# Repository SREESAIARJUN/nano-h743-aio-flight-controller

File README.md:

# STM32H743 Nano Flight Controller + 4-in-1 ESC AIO

**Autonomous Engineering Release - Cycle 31**  
*Dense 36 × 36 mm AIO (30.5 × 30.5 mm M3 mount) for ArduPilot & PX4 with Integrated 4x 20A/35A ESC. Rev 8.0 moved off the 25.5 mm outline because 24 SOP-Advance MOSFETs cannot fit on it; see the Rev 8.0 changelog.*

---

## 1. System Overview
- **MCU**: STM32H743VIT6 (480 MHz ARM Cortex-M7, 2MB Flash, 1MB RAM, Double-Precision FPU), clocked from a 24 MHz HSE crystal. 480 MHz requires revision V silicon.
- **PCB Stackup**: 6 layers, JLCPCB JLC061612-1080, 1.614 mm, ENIG. 1 oz outer for signals and fine pitch, 2 oz inner planes (In1 GND / In2 VBAT / In3 VBAT / In4 GND), filled-and-capped via-in-pad (POFV, IPC-4761 Type VII). Through vias only, no HDI microvias.
- **Dual IMUs**:
  - Primary: ICM-42688-P on high-speed SPI1 with isolated ground plane and silicon damping pads.
  - Secondary: ICM-42688-P on SPI4 for redundancy and sensor voting.
- **Barometer**: Bosch / Infineon DPS310 high-precision baro on I2C1 with acoustic dampening.
- **OSD**: AT7456E analog OSD on SPI2 + dedicated 6-pin SH1.0 connector for DJI O3 / Walksnail Avatar / HDZero digital VTX.
- **DroneCAN / UAVCAN**: On-board TCAN334 CAN FD transceiver on FDCAN1.
- **Blackbox**: MicroSD card slot with 4-bit high-speed SDIO (SDMMC1).
- **Integrated 4-in-1 ESC**:
  - 4x Brushless ESC channels, 2S–4S LiPo input. **Rev 9 thermal rating per motor, all four loaded, 24 kHz PWM:** 20 A continuous / 25 A for 10 s in typical prop wash; 16 A / 21 A in the pessimistic case. 35 A is held for only ~2.4 s, and only ~8 A is allowed on a static bench. These figures require 12 AWG battery and 20 AWG motor leads. Rev 9 lowered them from 20/28 and 17/22 A once the FD6288Q's built-in dead time was included in the loss model.
  - 24x Toshiba TPHR8504PL 40 V N-MOSFETs, SOP Advance. RDS(on) max 0.85 mΩ at VGS=10 V and 1.40 mΩ at 4.5 V, Rth(ch-c) 0.88 K/W. ESC1/2 sit on the top face and ESC3/4 on the bottom; each half-bridge site is shared by both faces, and every high-side pair has a 16-via POFV thermal array.
  - 4x AT32F421K8U7 ESC MCUs running AM32 (target `NANO_H743_AIO_F421`), each driving one FD6288Q 3-phase gate driver. The FD6288Q has no internal bootstrap diode, so each phase has an external low-leakage Schottky, 2.2 Ω and 2.2 µF. Each gate has a 0 Ω series footprint (kept so the slew rate can be re-tuned at bring-up) and a 2.2 nF C0G Cgs. AM32 `DEAD_TIME 43` (358 ns) adds to the driver's fixed 100–300 ns dead time. The FC battery failsafe `BATT_CRT_VOLT 6.4` protects the driver's UVLO (Rev 9).
  - 0.5 mΩ shunt resistor with INA226 / INA169 current monitor. **Rev 8 finding:** at 4 × 20 A, D=0.9 (72 A battery current) it dissipates 2.6 W, which is over the 2 W rating previously specified. It needs a ≥ 4 W part or 0.25 mΩ; this is an open item.
  - Support for BLHeli_32 / AM32 firmware, DShot300/600/1200, and bi-directional DShot RPM filtering.

---

## 2. Repository Contents
- `kicad/`: KiCad 8 project. The schematic covers the MCU core (Rev 7). The 6-layer PCB has the stackup, planes and the 24-MOSFET power stage (Rev 8); the other functions are not placed yet. Project footprint library `nano-h743-aio.pretty`, custom DRC rules `nano-h743-aio.kicad_dru`.
- `kicad/gerbers/`: Gerber X2 for 6 copper layers plus paste, mask, silk and edge, Excellon PTH/NPTH with drill maps, and a Gerber job file carrying the stackup. These are a power-stage fab preview, **not a releasable board yet** (see Rev 8.0 open items).
- `ardupilot/`: ArduPilot board definition `hwdef.dat`, bootloader `hwdef-bl.dat`, and board `defaults.parm`.
- `tools/validate_dma.py`: DMA-allocation validator that runs ArduPilot's own `chibios_hwdef.py` / `dma_resolver.py` and enforces the stream policy.
- `tools/gen_mcu_core_sch.py`: generates the MCU-core schematic, project symbol library and `sym-lib-table` from `ardupilot/hwdef.dat` (Rev 7).
- `tools/verify_mcu_core_sch.py`: schematic gate covering KiCad ERC, netlist topology of the HSE and VDDA circuits, and the hwdef ↔ schematic pin map (Rev 7).
- `analysis/hse_vdda_analysis.py`: design check for the 24 MHz crystal and the VDDA filter (clock tree, load capacitance, gm_crit, drive level, LC damping). Writes `analysis/hse_vdda_report.json`.
- `am32_esc/am32_target.h`: AM32 `Inc/targets.h` block for the AT32F421 + FD6288Q channel (Rev 9).
- `am32_esc/gate_drive_design.py`: FD6288Q/TPHR8504PL gate-drive design (gate-resistor sweep, dead-time derivation, DTG encoding, driver and bootstrap checks). It checks `am32_target.h` and `eeprom_settings.json` against the derived values and writes `gate_drive_report.json`, which the thermal model reads (Rev 9).
- `am32_esc/eeprom_settings.json`: the AM32 EEPROM fields the analysis depends on (PWM frequency, complementary PWM, minimum duty, brake dead-time override, cutoffs), with offsets (Rev 9).
- `tools/am32_build_target.sh`: splices the target into an AM32 checkout, builds it with AM32's pinned toolchain, checks the resolved macros and runs a SITL twin (Rev 9).
- `tools/gen_power_stage_pcb.py`: generates the footprint library, DRC rules, project rules and the 6-layer board (Rev 8).
- `tools/verify_power_stage_pcb.py`: PCB gate covering stackup, MOSFET population, thermal via geometry, through-hole net safety, topology, DRC with a rule-liveness check, regeneration, fab outputs and the thermal report (Rev 8).
- `analysis/thermal_power_analysis.py`: per-MOSFET loss model and a thermal network that reads its geometry back from the KiCad board. Writes `thermal_report.json` and `thermal_dissipation_curve.png` (rewritten in Rev 8).
- `firmware/bdshot_telem/`: bidirectional DShot telemetry reference in C++. It is bit-exact with ArduPilot's GCR/eRPM decode, and adds EDT decoding, round-robin health and plausibility tracking, and notch planning. `make test` runs 46 checks under ASan/UBSan (Rev 10).
- `tools/validate_bdshot.py`: bidir-DShot gate run against an ArduPilot tree. It covers the generated DMA/IC config, capture coverage, parameter validity, a bit-exact decoder cross-check, unit tests, analysis gates and the upstream patch (Rev 10).
- `analysis/bdshot_timing_analysis.py`: TIM1/DShot600/GCR timing, round-robin eRPM rates, notch-lag sweep over `SERVO_DSHOT_RATE`, quantisation and line electricals. Writes `bdshot_report.json` (Rev 10).
- `ardupilot/patches/`: upstream ArduPilot fix for bdshot `RECV_FAILED` error attribution (Rev 10).

---

## Revision 10.0 Engineering Changelog

**Scope:** Bidirectional DShot600 RPM filtering. Covers the ArduPilot TIM1 timer-channel and input-capture configuration, and processing of the ESC telemetry fed back from the motors. Every claim below was checked against ArduPilot 4.7.1 source (`AP_HAL_ChibiOS/RCOutput_bdshot.cpp`, `RCOutput.cpp`, `chibios_hwdef.py`, `dma_resolver.py`, `Filter/HarmonicNotchFilter.cpp`, `AP_ESC_Telem`, `AP_Vehicle`). An independent adversarial review then went over the claims, and its corrections are included.

### Changes implemented

**1. TIM1 timer-channel / input-capture configuration (`ardupilot/hwdef.dat`).** The pin assignment stays `PE9/PE11/PE13/PE14 = TIM1_CH1..CH4`, with `BIDIR` on CH1 and CH3. The block now records why that set is complete and how it actually works, and `tools/validate_bdshot.py` proves it against the generated `hwdef.h`:
- **Capture pairing.** `bdshot_setup_group_ic_DMA()` captures a channel with no IC DMA of its own on its partner's capture unit: CH2 on IC1 with `CC1S=10` (TI2→IC1), and CH4 on IC3. Pairing only exists within CH1/CH2 and CH3/CH4, so BIDIR on 1 and 3 covers all four motors. No `CHxN` outputs are used, because ArduPilot cannot input-capture them.
- **DMA.** `dma_resolver.py` places `TIM1_CH1` and `TIM1_CH3` on the `TIM1_UP` stream (DMA1-0). RCOutput re-points the DMAMUX request from UP to CHx for each receive window (`has_shared_ic_up_dma()`). The whole motor group still costs one stream, and `SHARED_DMA_MASK` stays 0.
- **Round-robin (new finding).** One timer group captures **one** motor's reply per DShot frame (`bdshot.curr_telem_chan`, `bdshot_find_next_ic_channel()`). With all four motors on TIM1, each motor's eRPM refreshes at f_DShot / 4. Earlier revisions did not account for this.
- **Timing at 480 MHz** (TIM1 kernel clock 240 MHz):

| Quantity | Value | Source |
|---|---|---|
| DShot600 output | PSC 49 → 4.8 MHz, 8 ticks/bit, exact | `setup_group_DMA`, `DSHOT_BIT_WIDTH_TICKS` |
| Command frame | 16 + 1 + 2 slots = 31 µs | `dshot_bit_length`, `pulse_send_time_us` |
| GCR reply | 750 kbit/s, 21 bits = 28 µs, ~30 µs after the frame | `bdshot_get_output_rate_hz` (5/4) |
| Capture prescaler | `telempsc` = 19 → 83.3 ns/tick, **exactly 16 ticks per GCR bit** | `RCOutput_bdshot.cpp:300` |
| Receive window | 31 + 30 + 10 = 71 µs (the reply needs 58 µs) | `bdshot_receive_pulses_DMAR` |
| Bidir cycle | 102 µs of a 625 µs frame period (16 %) | |

- **Electrical.** In bidir mode ArduPilot configures the pins as PUSHPULL + PULLUP at OSPEED MID1. The 40 kΩ internal pull-up settles the idle level within 2.8 µs (5τ), well inside the 30 µs turnaround.

**2. DShot series termination in the schematic (`tools/gen_mcu_core_sch.py`).** Added R4–R7: 100 Ω 0402, UNI-ROYAL 0402WGF1000TCE, LCSC C25076 (JLC basic part). Each sits in series on `TIM1_CHn → ESCn_DSHOT` and goes within 3 mm of U1. With ~14 pF of line capacitance, the RC is 1.4 ns (3.1 ns 10–90 %), which is < 2 % of a GCR bit. The resistors damp the ringing from MID1 edges into the ESC MCU input, and limit the current when the FC and ESC both drive the line during turnaround. **No external pull-up was added on purpose.** ESC bootloaders treat a signal line that is high at power-on as a host waiting for 1-wire passthrough. `verify_mcu_core_sch.py` gained the matching netlist, value, MPN and BOM checks, plus a new S8 check that R4..R7 follow hwdef `PWM(1..4)` order to `ESC1..4_DSHOT`.

**3. Parameters (`ardupilot/defaults.parm`).**

| Parameter | Rev 6–9 | Rev 10 | Reason |
|---|---|---|---|
| `SERVO_DSHOT_RATE` | 0 (default) | **4** | Rate 0 sends on every loop push and also on 1 ms timer ticks that each push re-arms, giving uneven 0.5 / 1 / 1 ms spacing (~1.2 kHz). Rate 4 sends a frame every 625 µs, phase-locked to the 400 Hz loop. That gives **400 Hz per motor** under round-robin, the fastest of rates 0–4, and ArduPilot keeps loop × rate ≤ 4096 Hz. |
| `INS_HNTCH_OPTS` | 2 | **6** | Adds bit 2, loop-rate update. Without it the notch is re-centred only when more than 5 ms have passed, which is every 3rd loop (~133 Hz). |
| `INS_HNTCH_HMNCS` / `ATT` | implicit | 3 / 40 | Now explicit. At `INS_GYRO_RATE` 2 kHz, the 2nd harmonic of motors above 480 Hz is past the 0.48 × 2 kHz = 960 Hz Nyquist guard and is skipped. |
| `SERVO_DSHOT_ESC` | 3 | 3 | Documented: ArduPilot sends DShot command 13 to enable EDT, and AM32 then interleaves temperature, voltage and current frames. |

Behaviour below `INS_HNTCH_FREQ` 80 Hz was derived from `HarmonicNotchFilter`. The notch is held at 80 Hz, and its **linear** gain A, not its dB depth, is interpolated towards 1. At 50 Hz this leaves 10.4 dB, not "half of 40 dB". Below 20 Hz the notch is disabled.

**4. ESC telemetry processing reference (`firmware/bdshot_telem/`, C++17, no allocation).**
- `decode_gcr_edges()` is **bit-exact** with `RCOutput::bdshot_decode_telemetry_packet()`. `validate_bdshot.py` V4 extracts the upstream function from the ArduPilot tree, compiles it next to ours and compares 421 184 cases: all payloads × ±6–19 % clock error, jitter, dropped and extra edges, and 200 000 random edge trains. **0 mismatches.** The review caught a divergence on reversed (synthetic) edge intervals, where ArduPilot's signed/unsigned arithmetic yields len 0. That behaviour is now reproduced. Cortex-M7 `LSL` semantics are modelled for upstream's `1U << (len-1)` with len = 0.
- `decode_payload()` covers eRPM and EDT (temperature, voltage, current, debug, v2 stress and status). It keeps ArduPilot's uint16 truncation and the `ZERO_ERPM` case, and adds a distinct `ZeroPeriod` frame type, which ArduPilot counts as clean but which carries no RPM.
- `MotorTelemetryMonitor` tracks staleness with round-robin awareness: a dead ESC is flagged after 3 of its own slots, i.e. 12 frames or 7.5 ms. It also adds a **plausibility gate** that ArduPilot lacks: CRC-valid eRPM with a period under 100 µs is rejected. The 4-bit CRC lets ~5 % of heavily corrupted frames through (test T4), and periods under 10 µs wrap in ArduPilot's uint16 arithmetic. Example: a 9 µs frame reads as 113 100 eRPM.
- `plan_notches()` mirrors the HarmonicNotchFilter centre, Nyquist, minimum-frequency, fade and disable rules for 16 harmonics, capped at `HAL_HNF_MAX_FILTERS` = 54.

**5. Upstream ArduPilot defect + patch (`ardupilot/patches/0001-…patch`).** `bdshot_finish_dshot_gcr_transaction()` rotates `curr_telem_chan` *before* `bdshot_prepare_for_next_pulse()` books the result. `RECV_FAILED` (no edges, i.e. the ESC is silent) is then booked on `curr_telem_chan`, which is the **next** motor. A dead ESC2 therefore inflates ESC3's logged error rate. The patch books the failure on `group.chan[prev_telem_chan]` and applies the 5 s statistics reset on that path as well. Without the reset, the silent channel's uint16 counter would grow until it wraps. The patch applies cleanly (V7). The defect is reproduced in a host model of the counter logic (T8), not on hardware.

**6. Timing analysis (`analysis/bdshot_timing_analysis.py` → `bdshot_report.json`).** The rate sweep uses ArduPilot's own scheduling model. The notch-lag column is the age of the RPM the notch actually uses: round-robin wait + `AP_ESC_Telem::get_rpm()` interpolation (one more update period) + loop consumption + AM32's 6-commutation average (0.43 ms). Punch lag assumes a full punch of ~9.4 kHz/s mechanical-frequency slew.

| `SERVO_DSHOT_RATE` | Frames | Spacing | Per-motor eRPM | RPM age | Punch lag |
|---|---|---|---|---|---|
| 0 | ~1200 Hz | 0.5 / 1 ms, uneven | 300 Hz | 9.8 ms | 92 Hz |
| 1, 2 | 800 Hz | 1.25 ms | 200 Hz | 12.9 ms | 122 Hz |
| 3 | 1200 Hz | 0.83 ms | 300 Hz | 9.6 ms | 91 Hz |
| **4** | **1600 Hz** | **0.625 ms** | **400 Hz** | **7.9 ms** | **75 Hz** |

eRPM quantisation is ≤ 0.40 % (0.12 Hz) from 1 500 to 42 000 RPM, and the slowest representable speed is 131 RPM.

### Architecture improvements
- The FC/ESC telemetry contract is now one checked chain: `hwdef.dat` (pins, BIDIR pairing) → generated `hwdef.h` (DMA) → `defaults.parm` (rates, notch) → AM32 EEPROM `motor_poles` (`am32_esc/eeprom_settings.json`) → schematic R4–R7. `validate_bdshot.py` fails if any link drifts.
- `defaults.parm` is validated against the real ArduPilot `@Param` documentation (names, `@Values`, `@Bitmask`, `@Range`), instead of trusting comments.
- AM32-side assumptions are corrected. EDT is off in AM32 until DShot command 13, and AM32 auto-detects the DShot rate, so neither is a compile-time macro. The eRPM period is independent of AM32's `motor_poles`, so only the FC's `SERVO_BLH_POLES` sets the notch frequency.

### Validation status
- `python3 tools/validate_bdshot.py --ardupilot <ArduPilot 4.7.1>`: **PASS**. V1 generation and DMA, V2 capture coverage and BDMASK, V3 all 15 parameters valid, V4 0/421 184 mismatches, V5 46/46 unit checks under ASan + UBSan, V6 all analysis gates, V7 the patch applies.
- `make -C firmware/bdshot_telem test`: **PASS** (46 checks). This includes the exhaustive GCR round trip and decoding with up to ±14 % ESC bit-clock error.
- `python3 tools/validate_dma.py`: **PASS**, unchanged DMA map with 12/16 streams.
- `python3 tools/verify_mcu_core_sch.py`: **PASS** on the Rev 10 hwdef pin set (ERC 0 errors, exact netlist with R4–R7, new S8 check). *Working-tree note:* concurrent Rev 11 edits add `PE1 IMU2_DRDY` / `PD12 IMU_CLKIN_MON` to `hwdef.dat` before the schematic has been regenerated, so S1/S6 fail until `tools/gen_mcu_core_sch.py` is re-run as part of that work.
- `tools/verify_power_stage_pcb.py`: 2 **pre-existing** failures (the Gerber file set and silkscreen re-plot have been out of step since Rev 9). Rev 10 does not touch the PCB.

### Open items
- **Hardware not yet verified:** scope the GCR reply at the H743 pin to confirm the 30 µs turnaround and edge quality through R4–R7. Fly a log with `INS_LOG_BAT_OPT` 4 (pre/post filter) to confirm notch placement.
- The notch cannot follow a full-throttle punch at any DShot rate: it lags by ≥ 75 Hz and keeps < 1 dB of depth during the ~60 ms slew. Options are a higher `SCHED_LOOP_RATE`, or splitting the motors over two timers (two captures per frame). The second needs a pin change, because PE9/11/13/14 are TIM1-only.
- Submit the `RECV_FAILED` patch upstream.
- Leave PCB placement for R4–R7 to the signal-layout revision.

---

## Revision 9.0 Engineering Changelog

**Scope:** AM32 ESC firmware target for the FD6288Q gate drivers: the dead-time generator setting and slew-rate (gate network) tuning.

### Changes implemented

**1. A real AM32 target in place of a placeholder.** The Rev ≤ 8 `am32_esc/am32_target.h` defined `DEAD_TIME_NS 60`, `PWM_FREQ_KHZ 48`, `TEMPERATURE_CUTOFF_C`, `BIDIRECTIONAL_DSHOT` and similar macros. AM32 reads none of them. The board also had no ESC MCU, and AM32 cannot run on the H743. Rev 9 picks the **AT32F421K8U7** (one per motor). AM32 has 86 F421 targets, the MCU's TMR1 runs at 120 MHz (8.33 ns dead-time resolution), and it costs under $1. The new file is a drop-in `Inc/targets.h` block, checked against AM32 v2.21 (3d8cd50):

| Macro | Value | Why |
|---|---|---|
| `FILE_NAME` / `FIRMWARE_NAME` | `NANO_H743_AIO_F421` / `NanoH743AIO` | `_F421` suffix makes `make` discover the target. The name must be ≤ 12 characters (`_Static_assert`, main.c:351) |
| `HARDWARE_GROUP_AT_B` | — | Complementary TMR1 pairs: HIN A/B/C ← PA10/PA9/PA8 (CH3/2/1), LIN A/B/C ← PB1/PB0/PA7 (CH3N/2N/1N). Signal input PB4 (TMR3_CH1) |
| `HARDWARE_GROUP_AT_045` | — | Back-EMF comparator A = PA0, B = PA4, C = PA5 |
| `DEAD_TIME` | **43** | Raw TMR1_BRK.DTC code: 43 × 8.333 ns = **358.3 ns**. Derived in section 3 |
| `TARGET_VOLTAGE_DIVIDER` | 110 | 100 k / 10 k on PA3. AM32 scales V × 10, full scale 36.3 V |
| `CURRENT_OFFSET` / `MILLIVOLT_PER_AMP` | 0 / 20 | There is no per-channel current amplifier. PA6 is grounded through 10 k, so AM32 reports 0 A |
| *not defined* | `USE_INVERTED_*`, `USE_OPEN_DRAIN_*`, `PWM_ENABLE_BRIDGE`, `USE_SERIAL_TELEMETRY` | FD6288Q **HIN and LIN are both active-high** (datasheet V1.6 §1.3: "output in phase with input"; Table 1-2). Telemetry is extended DShot telemetry over the signal wire (Rev 10) |

**2. Slew-rate tuning: the gate network is chosen by a calibrated sweep (`am32_esc/gate_drive_design.py`).** The script integrates the TPHR8504PL gate-charge curve (Qgs1 25 nC, Qgd 12.4 nC, Qg 103 nC at 10 V). The Miller plateau depends on current, temperature and Vth corner (Fig. 8.1, shifted by −8.5 mV/K and by Vth,min − Vth,typ). The FD6288Q is modelled as a resistive output (VOH/VOL ⇒ 6/9 Ω source, 3/4.5 Ω sink) **limited to its rated IOH/IOL** (1.1–1.9 A / 1.3–2.3 A, scaled down below VCC 15 V). Calibrated against Toshiba's switching test circuit, the model gives turn-on 25.9 ns vs 26 ns and turn-off 98.6 ns vs 63 ns, so it errs slow on turn-off, which is the safe side for dead time. It sweeps 99 networks (Rg_on × {single R, Rg ∥ Schottky + R_off} × Cgs_ext). Each network is checked at the fast corner (4S HV 17.4 V, 35 A, 125 °C, Vth,min; the victim FET held off through rg_int,max) against four limits:

- dv/dt ≤ 5 V/ns
- Miller shoot-through energy ≤ 10 % of the turn-on energy
- VDS peak ≤ 32 V with a 3 nH loop
- FD6288Q Tj ≤ 125 °C at a 105 °C board

Selection rule: within 10 % of the minimum feasible loss, fewest parts per FET, then lowest dv/dt. Every gate keeps a series-resistor footprint.

| Network (per FET) | Switching loss per HS, 4S 20 A 24 kHz | dv/dt | Shoot-through E_st/E_on | Result |
|---|---|---|---|---|
| **0 Ω footprint + 2.2 nF C0G Cgs (selected)** | **117 mW** | **2.85 V/ns** | **5.2 %** | Selected: best shoot-through within the loss band |
| 0 Ω + 1.0 nF Cgs | 110 mW | 2.88 V/ns | 8.9 % | Feasible, less shoot-through margin |
| 15 Ω ∥ Schottky | 145 mW | 1.21 V/ns | 9.5 % | Feasible but +24 % loss |
| 4.7 Ω single (Rev 8 thermal assumption) | 183 mW | — | > 10 % | **Rejected:** shoot-through |
| 0 Ω, no Cgs | 106 mW | > 5 V/ns | > 10 % | Rejected |

With 0 Ω, the driver's current limit sets the slew rate. Gate-loop damping is still ζ ≥ 1.19 for a 10 nH loop (check C9). The 2.2 nF Cgs divides the Cdv/dt charge: induced Vgs is 1.07 V peak against Vth,min(125 °C) 0.55 V, with 0.39 µJ shoot-through per edge.

**3. Dead time is derived, not guessed.** The FD6288Q already inserts a fixed 100/200/300 ns interlock (min/typ/max, Table 3-4), so the MCU only covers the rest:

DT_mcu ≥ toff_prop,max + t_out(→ Vth,min,125 °C | slow) − (toff_prop,min + DT_int,min + t_in(→ Vth,min | fast)) + MT 30 ns + 25 ns guard

The worst case is evaluated over both transitions, with the outgoing FET hard-switched (at 10/20/35 A) or soft, at 4S HV and 2S min:

| Bus | Transition | Outgoing soft | Outgoing hard (10 A, plateau 1.67 V) |
|---|---|---|---|
| 4S HV | HS off → LS on | 324.8 ns | 349.8 ns |
| 4S HV | LS off → HS on (negative phase current: deceleration, braking) | 328.9 ns | **353.9 ns** |
| 2S min | HS off → LS on / LS off → HS on | 239.0 / 243.8 ns | 247.9 / 252.8 ns |

The requirement is 353.9 ns, which rounds up to **`DEAD_TIME 43` = 358.3 ns**. It is in the linear DTC range (< 128), and the same encoder/decoder handles codes ≥ 128. Body-diode conduction per edge (outgoing channel off → incoming channel on) is **457 ns typ / 755 ns max**. The thermal model uses the max.

**4. EEPROM settings AM32 actually reads (`am32_esc/eeprom_settings.json`, offsets from `Inc/eeprom.h`).**
- `pwm_frequency` 24 kHz, `variable_pwm` 0, `comp_pwm` 1.
- `minimum_duty_cycle` **4**. AM32 duty runs 0..2000 of ARR, so this gives 842 ns. The AM32 default of 1 gives 208 ns, which is shorter than the 688 ns worst-case dead time, so the shortest pulses would vanish.
- `driving_brake_strength` **10**. Strengths 1–9 **OR** (`BDTR |=`, main.c:708) `DEAD_TIME + 150 − 10·s` into the register, which gives a non-monotonic 0.93–2.12 µs.
- `low_voltage_cut_off` **0**. AM32's cutoff latches `allOff()` on one ESC until power cycle, and mode 1 guesses the cell count once at arming. The FD6288Q UVLO floor is enforced by the FC instead: `BATT_CRT_VOLT 6.4` / `BATT_FS_CRT_ACT 1` (Land), added to `ardupilot/defaults.parm`.
- `limits.temperature` 115 °C. This is the uncalibrated AT32 die sensor with a last-resort step derate.
- `limits.current` 0.
- `motor_poles` 14, matching `SERVO_BLH_POLES`.

**5. Gate-drive hardware requirements (report `requirements`, for the ESC schematic sheet).**
- FD6288Q VCC = VBAT through 10 Ω, with 10 µF and an 18 V Zener. The HS bootstrap can pump to 20.9 V on a −4 V VS undershoot, against VGSS 20 V.
- Bootstrap per phase: 40 V Schottky with IR ≤ 100 µA at 105 °C, 2.2 Ω in series, and 2.2 µF/25 V. The worst-case HS on-time without refresh is 1.25 ms at 2S (≥ 2.3 k rpm at 100 % duty), 13.6 ms at 3S and 25.9 ms at 4S, including IQBS, diode leakage and the 100 k HS pull-down.
- Pull-downs: 10 k on each LS, 100 k on each HS.
- Commutation loop ≤ 3 nH.

**6. Thermal model updated (`analysis/thermal_power_analysis.py`).** It reads `gate_drive_report.json` as the single source of truth:
- HS switching energy now comes from the simulator's (I, Vbus) table instead of the optimistic Qsw/I_plateau formula.
- Body-diode window: 755 ns, not the Rev 8 value of 60 ns.
- Gate power now includes Cgs.
- RDS(on) tempco corrected from 0.0056 to 0.0072 /K (Fig. 8.9).
- Miller plateau 3.0 → 3.3 V.
- Datasheet citation corrected to Rev.5.0 (2019-10-24).

**The published per-motor ratings drop from 20 A / 28 A (typical) and 17 A / 22 A (conservative) to 20 A / 25 A and 16 A / 21 A.** The search confirms these are the largest whole-amp values that pass (17, 22 and 26 A fail).

### Architecture improvements
- **Single source of truth, closed loop.** Datasheet tables feed `gate_drive_design.py`, which writes `gate_drive_report.json`. That report feeds the thermal model, and the thermal model feeds the published ratings, which `verify_power_stage_pcb.py` P11 checks. The script also checks the header (H1–H7: DEAD_TIME, groups, polarity, names, divider, dead macros, quoted ns figures), the EEPROM file (E1–E2) and `defaults.parm` (E3, SERVO_BLH_POLES). Hand-editing any of them breaks the gate.
- **Real-toolchain build gate.** `tools/am32_build_target.sh <AM32>` copies AM32, splices the block in before AM32's "Missing defines" guard, and installs AM32's pinned xPack GCC 10.3.1. It then builds `NANO_H743_AIO_F421`, asserts 34 resolved macros from `arm-none-eabi-gcc -E -dM` (pins, comparator, clock, DEAD_TIME, absent inversion macros), and runs a SITL twin to confirm the DTC code reaches the timer's BDTR unchanged.

### Validation status

| Check | Result |
|---|---|
| `python3 am32_esc/gate_drive_design.py`: C0 calibration, C1–C3, C9 slew/damping, C4 DTG, C5–C8 supply/driver/bootstrap, H1–H7 header, E1–E3 EEPROM/FC | **PASS** (20/20) |
| Mutation tests on that gate (13 cases): old DEAD_TIME 34, stale header ns, `USE_INVERTED_HIGH`, LVC on, AM32-default min duty, brake 5, variable PWM, BATT_CRT_VOLT 5.5, FS action 0, model without IOL cap, model without LS-hard rows, 10 k HS pull-down, 40 nH gate loop | **every mutation caught**; the unmodified control passes |
| `tools/am32_build_target.sh /tmp/AM32` (AM32 v2.21) | **PASS**: 21,284 B flash (77 % of 27 KB), 3,680 B RAM, all 34 macros resolved. SITL: `dead time 268ns (BDTR 0x2b)` (SITL clock 160 MHz; on the F421 at 120 MHz, 0x2B = 358 ns) |
| `python3 analysis/thermal_power_analysis.py` | **PASS** at 16/21/20/25 A. Conservative 10 s burst ends at 109.4 °C board against a 110 °C limit: 0.6 K margin |
| `python3 tools/verify_power_stage_pcb.py` P11 (thermal report re-run identical, ratings hold) | **PASS**. The 2 P10 Gerber failures predate this revision; Rev 9 changes no PCB file |
| Independent 3-lens adversarial review (physics, AM32 semantics, thermal coupling), each finding verified by a separate refuter | 11 confirmed, 10 refuted. **All 11 fixed:** IOL/IOH current caps, LS hard-turn-off rows, corner-consistent plateau, rg_int,max on the Miller victim, bootstrap pull-down and leakage, latching LVC replaced by FC failsafe, min-duty units, thermal switching energy from the simulator, temperature-limit wording, header ns figures |
| `BATT_CRT_VOLT` / `BATT_FS_CRT_ACT` names | Present in upstream `AP_BattMonitor_Params.cpp` (Copter: 1 = Land) |
| Hardware | **Not run.** Bring-up must measure: dead time on the HO/LO pins at 4S under load (expect ≥ 358 ns MCU + driver interlock); switch-node dv/dt and VDS overshoot at 35 A (≤ 2.9 V/ns, ≤ 24 V); LS gate bounce during HS turn-on (≤ 1.1 V); AT32 die-sensor offset to the board |

**Open items.**
- **FD6288Q supply:** LCSC C328453 shows 0 in stock. The AT32F421K8U7 QFN has 39.
- **Model inputs to confirm:** the FD6288Q output resistance and the minimum turn-off propagation delay are not in the datasheet. They are derived or assumed and flagged in the report.
- **Vth tempco:** the design is sensitive to it. At −12 mV/K instead of −8.5 mV/K, no network meets the shoot-through limit. Confirm it against Toshiba data.
- **ESC schematic:** the sheet with the parts above is still to be drawn.
- **Burst margin:** the 0.6 K margin on the conservative burst rating is thin.

---

## Revision 8.0 Engineering Changelog

**Scope:** KiCad 8 6-layer PCB with a 2 oz inner copper plane stackup, and thermal vias under the 24× TPHR8504PL MOSFETs.

### Changes implemented

**1. A real 6-layer stackup in place of a label.** Before Rev 8, `nano-h743-aio.kicad_pcb` was an empty outline: six copper layers with no stackup definition, so the Gerber job file reported 35 µm everywhere. The board now carries JLCPCB's orderable **JLC061612-1080** stackup, which is written into the board and the Gerber job file:

| Layer | Copper | Dielectric to next layer | Use |
|---|---|---|---|
| L1 F.Cu | 1 oz (35 µm) | 0.1375 mm 1080×2 prepreg, εr 3.91 | FETs ESC1/2, phase pours, signals |
| L2 In1.Cu | **2 oz** (61 µm finished) | 0.35 mm core, εr 4.6 | **GND plane**. Reference for L1, HSE/VDDA return from Rev 7 |
| L3 In2.Cu | **2 oz** | 0.325 mm 1080+7628+1080, εr 4.24 | **VBAT plane** |
| L4 In3.Cu | **2 oz** | 0.35 mm core | **VBAT plane** |
| L5 In4.Cu | **2 oz** | 0.1375 mm 1080×2 | **GND plane**. Reference for L6 |
| L6 B.Cu | 1 oz | — | FETs ESC3/4, phase pours |

The stackup totals 1.614 mm, with an ENIG finish and filled-and-capped via-in-pad (POFV, IPC-4761 Type VII), which JLC includes free on 6-layer boards. Outer copper stays at 1 oz on purpose. The LQFP-100 has a 0.5 mm pitch, and 2 oz outer copper would push it to JLC's 0.15–0.2 mm 2 oz trace and space limit. GND/VBAT/VBAT/GND gives two GND–VBAT pairs 0.35 mm apart for the hot loop, two parallel 2 oz layers per rail (0.14 mΩ/sq each), and a solid GND reference directly under both outer signal layers.

**2. The 24 MOSFETs did not fit on a 25.5 mm board, so the outline moved to 36 × 36 mm with a 30.5 × 30.5 mm M3 mount.** The previous outline was 25.5 mm square with holes 20 mm apart, inconsistent with its own "25.5 mm" label. On Toshiba's land pattern, a TPHR8504PL needs 38.7 mm² of courtyard, so 24 of them need 929 mm². A 25.5 mm square has 650 mm² per side before the LQFP-100, which takes about 290 mm² more. The fit check is built into the generator, and its result made 30.5 mm-class the smallest standard frame size that works.

**3. Project footprint library (`kicad/nano-h743-aio.pretty`).** The land pattern is Toshiba's recommended SOP Advance (2-5Q1S) pattern. The research reviewer found that the LCSC/EasyEDA footprint for C5331611 is actually a Diodes PowerDI5060 footprint, so it isn't used. The pattern details:

- G/S pads: 0.85 × 1.45 mm on a 1.27 mm pitch.
- Gap to the drain: 0.7 mm.
- Drain land: 4.7 × 4.8 mm, with four 0.85 mm fingers for pins 5–8 (pin 5 sits opposite pin 4).
- Paste: 2 × 2 windowpane at 69 % coverage.
- Zone connection: solid, set on the footprint.

There are three variants:
- `…_ThermalVias_4x4`: 16 × 0.30/0.50 mm POFV vias in the drain body, on a 1.27 × 1.0 mm pitch.
- `…_SourceVias_2x2`: 4 POFV vias in source pads 2 and 3.
- Plain.

The same five-file library also holds `MountingHole_3.2mm_M3_Grommet_Keepout` and `MotorPad_4.0x1.3mm`.

**4. Power-stage layout (`tools/gen_power_stage_pcb.py`).** The layout is placed in a single frame of reference along the board edge, then rotated onto the N, S, W and E edges. Each of the 444 pad positions is checked against a closed-form transform at generation time. Six half-bridge sites each hold one top half-bridge (ESC1/2) and one mirrored bottom half-bridge (ESC3/4) at the same XY position:

- **H slot.** The top and bottom high-side drains are both VBAT, so they share one 16-via POFV array. The array connects solidly to In2/In3 and to both drain tabs. Every high-side FET therefore gets a thermal-via array, while only 96 drills are needed for 12 high-side FETs.
- **L slot.** The top and bottom low-side sources are both GND. Mirroring makes top pins 2/3 coincide with bottom pins 3/2, so 4 in-pad POFV vias serve both FETs. A row of 3 return vias just inboard, tied to both faces by 0.6 mm tracks, brings the total to **7 GND vias per low-side pair**. Without that row, the four barrels would carry about 16 A RMS combined at 20 A.
- **No drain vias on the low-side FETs, by design.** The top and bottom low-side drains are phase nodes of different ESCs, so any through via under one would short it to the other. Their heat path is the L1/L6 phase pour plus the 0.1375 mm prepreg into the In1/In4 GND plane, modelled at 8.3 K/W. Any other arrangement costs a third slot per phase, which doesn't fit.
- **Phase pours.** On the top face, the high-side sources (pins 1–3) face the low-side drain across a 0.7 mm gap, so the pour bridges them directly. On the mirrored bottom face, the gate pad sits on that side, so the pour runs through the motor-pad strip. That leaves the gap free as the bottom gate's escape channel. A second 0.7 mm channel on the far side serves the top gate.
- **Motor pads.** Each phase has a 4.0 × 1.3 mm wire pad at the board edge, inside its own pour.
- **Mounting holes.** Each M3 hole has a 6.4 mm grommet keep-out on all copper.
- **MCU area.** A 15.7 mm square is reserved for the MCU and marked on Cmts.User.

**5. Thermal relief policy: the MOSFETs get solid connections, not spokes.** A 4-spoke relief in 2 oz copper adds 9–18 K/W per layer, which is two to four times the whole via-array resistance. All Q* and motor pads therefore connect solid. This is set on the footprint and enforced by a `.kicad_dru` rule. The planes keep 0.25 mm gap / 0.4 mm spoke reliefs for any future through-hole parts, which need them to solder.

**6. Custom DRC rules (`kicad/nano-h743-aio.kicad_dru`):**
- 2 oz inner layers: clearance 0.2 mm, width 0.16 mm, hole-to-copper 0.2 mm.
- Solid zone connection on Q* and MP*.
- POFV drill must be exactly 0.30 mm.
- NPTH grommet clearance 0.5 mm.

**Defect found while building this:** the rules file originally had no units, and **KiCad then ignores the whole file without warning**. `kicad-cli` reported a clean DRC while no custom rule was active. The rule-liveness gate caught it. The fix: every value now carries `mm`, and the verifier also requires the file to parse in pcbnew's DRC engine.

**7. Thermal analysis rewritten (`analysis/thermal_power_analysis.py`).** Several defects in the Rev ≤ 7 script are fixed:

- It multiplied the **total board loss by a single θJA**, so four ESCs were treated as one junction.
- It used 1.4 mΩ, the 4.5 V RDS(on), at every gate drive.
- It reported **218 °C** at 35 A as `CERTIFIED_SAFE_UNDER_FLIGHT_AIRFLOW`.

The new model:

- **Losses per FET, 6-step complementary PWM:** HS conduction I²R·D/3 and LS I²R·(2−D)/3, with RDS(on)(Tj) iterated. Switching losses use gate-charge transition times (t_on 19.7 ns, t_off 75 ns through the FD6288Q plus 4.7 Ω Rg). Also included: Coss/Qrr, the dead-time body diode, and gate drive (Qg(V)·V·fsw).
- **Board-level losses previously missing:** VBAT/GND plane I²R, the current shunt, and the 1 oz phase bridge (from the generator geometry; the bottom-face neck is narrower).
- **Thermal network read back from the KiCad file:**
  - junction-to-case (0.88 K/W) and SAC305 joint (0.08 K/W);
  - HS: 16 barrels down 0.58 mm to the nearest VBAT plane (5.9 K/W), in parallel with prepreg (20.3 K/W), giving 4.6 K/W;
  - LS: 8.3 K/W through prepreg;
  - radial spreading in the 4 × 2 oz planes: 0.81 K/W per site;
  - board-to-air on both faces with fin efficiency;
  - battery and motor leads as pin fins **with their own I²R generation**;
  - a lumped board capacitance and wire lags for bursts.
- **Via array ablation at the legacy 35 A point:** with the vias, the HS junction sits 4.3 K above its site; with prepreg only it would be 16.4 K. The array buys **12.2 K** per FET.

**8. Ratings corrected, and AM32 changed.**
- **The model does not support the old 20 A / 35 A claim under pessimistic cooling.** At h = 50 W/m²K and 20 A, the board reaches 118 °C, which trips AM32's 115 °C cutoff.
- **Published ratings (per motor, all four loaded, 4S, D = 0.9, 24 kHz, Tamb 35 °C, 12 AWG battery / 20 AWG motor leads):**
  - Typical prop wash (h = 80): **20 A continuous, 28 A for 10 s.**
  - Pessimistic (h = 50): **17 A, 22 A.**
  - 35 A is allowed for about 4 s (2 s in the pessimistic case).
  - Static bench: about 8 A.
- **`am32_esc/am32_target.h`:**
  - `PWM_FREQ_KHZ 48 → 24`. 48 kHz adds +2.6 W at the 20 A point, and the 28 A burst then ends at 118.9 °C, past the cutoff; at 24 kHz it ends at 109.2 °C.
  - The RDS(on) comment is corrected.
  - The 38 A over-current limit is documented as a stall/short trip, not a thermal rating.

### Architecture improvements

- **Generator-first PCB.** Following the Rev 7 schematic, the footprints, DRC rules, project rules and the filled board are all generated by code. The board is **byte-deterministic**: pcbnew's random KIIDs are replaced with content-derived uuid5 values, the board is reloaded, re-saved and rewritten, and the root sheet UUID in `.kicad_pro` is pinned to the schematic. A hand edit therefore shows up as a diff against regeneration. All footprints link to the `nano-h743-aio` library, so KiCad's library-parity DRC actually runs.
- **Planes stay continuous under the via arrays.** Via pads use `remove_unused_layers`, so each GND plane sees a 0.7 mm hole antipad instead of a 0.9 mm pad antipad. Before this fix, the 1.0 mm pitch columns merged into **3.9 mm slots in In1/In4 under every high-side array**. The review found this, and the verifier now samples between every adjacent via pair. GND plane fill went from 83 % to 85 %.
- **Power budget, from the model.** At 20 A typical, the board dissipates 12.3 W:
  - FETs 5.6 W
  - shunt 2.6 W
  - phase bridges 1.6 W
  - planes 1.4 W
  - gate drive 0.5 W
  - MCU and other 0.6 W

  So **at the rated point the via arrays aren't the bottleneck; board-level heat removal is.** The next gains are a lower-value shunt, 2 oz outer copper on the bridges, and harness/airflow.

### Validation status

| Check | Result |
|---|---|
| `python3 tools/verify_power_stage_pcb.py` (P1–P11, see the script header) | **PASS (0 failures)** |
| P1 stackup / planes | Matches JLC061612-1080, 1.614 mm, ENIG. In1/In4 GND 85 %, In2/In3 VBAT 87 % filled. No slots between thermal vias |
| P2–P6 population, thermal arrays, safety, topology | 24 FETs, 12 per side. 6 × 16 VBAT vias, each inside both high-side drains. 12 low-side FETs with ≥ 7 GND vias each. None of the 138 plated holes lands in a pad of another net. 12 phases, 24 unique gates, 12 motor pads |
| P8 `kicad-cli pcb drc --severity-all` | **0 violations, 0 unconnected**, with custom rules live. A planted 0.25 mm thermal via is flagged. The DRU parses in the pcbnew engine |
| P9 / P10 reproducibility and fab outputs | Board byte-identical to regeneration with a fresh fill. Exactly 18 fab files, each content-identical to a fresh `kicad-cli` re-plot. Job file: 6 layers, 1.614 mm, ENIG, copper 35/61/61/61/61/35 µm. 138 PTH hits plus 4 × 3.2 mm NPTH |
| P11 thermal | All five published-rating scenarios PASS. The committed report matches a re-run field by field |
| Verifier mutation tests (12 runs against a repo copy) | **11/11 defects caught**, no-op control passes. The defects: thermal-via pad resized; via made blind; one thermal via deleted; Q pad set to thermal relief; inner copper 0.035 mm; stale F.Cu Gerber; missing B.Mask; drill moved; hand-edited thermal report; rating raised to 25 A; DRU units dropped |
| Independent 4-lens adversarial review (geometry/DFM, thermal/electrical, verifier mutation, KiCad tooling), each finding re-verified by a refuter | 15 confirmed findings, all fixed or modelled; 1 refuted. Critical: wire fins credited for cooling while their own I²R heating was ignored. Major: the burst verdict ignored the AM32 cutoff; P9/P10 never checked pad, drill or Gerber content; stale fills; no library nickname on footprints; non-deterministic UUIDs. Also fixed: the GND plane slots, a narrow bottom phase bridge (widened to the gate-clearance limit and modelled), and a mismatched mounting-hole library zone |
| `python3 tools/verify_mcu_core_sch.py` (Rev 7 gate) | **PASS** with the Rev 8 project file |
| Hardware | **Not built.** Bring-up: IR camera at 20 A × 4 in a prop-wash rig (expect a board of about 87 °C at 35 °C ambient); confirm AM32 reads 24 kHz; keep bench runs to ≤ 8 A per motor without airflow |

**Open items (blocking a releasable board):**
- **MCU placement.** The 15.7 mm reserve can't hold an LQFP-100 land pattern with its decoupling. Either move to STM32H743**VIH6** (TFBGA-100, 8 × 8 mm), which needs a Rev 7 pin-map regeneration, or accept a 38 mm outline.
- **Unplaced parts.** Gate drivers, gate resistors, bulk and ceramic capacitors, shunt, current sensor, battery pads, IMUs and the rest. The 24 gate nets have reserved 0.7 mm channels but no routing. ESC schematic sheets are still to be drawn.
- **Shunt.** It needs a ≥ 4 W part, or 0.25 mΩ, which saves 1.3 W.
- **Package variant.** Confirm the TPHR8504PL reel is SOP Advance (2-5Q1S), not (N) 2-5W1A.
- **Unconfirmed driver data.** FD6288Q output resistance (6 / 4 Ω assumed) and the RDS(on) temperature slope are taken from typical curves. Re-run the analysis when confirmed.
- **Release prerequisite.** Confirm with JLC that their stackup with POFV supports 2 oz inner copper.

## Revision 7.0 Engineering Changelog

**Scope:** KiCad 8 schematic for the STM32H743VIT6 at 480 MHz, covering the external 24 MHz crystal oscillator, its load capacitance, and ferrite-bead filtering of VDDA.

### Changes implemented

**1. The 25 MHz HSE could never run at 480 MHz, so the crystal moved to 24 MHz.**
Rev 6 set `OSCILLATOR_HZ 25000000`. The README advertised 480 MHz, but ArduPilot's `stm32h7_mcuconf.h` has no PLL set for 25 MHz with a custom clock rate. It hits `#error "Unable to configure custom clockrate"`. I confirmed this by running the real header through `gcc -E` with `STM32_HSECLK=25000000U` and `HAL_CUSTOM_MCU_CLOCKRATE=480000000`. At 24 MHz the same header resolves to:

| PLL | Ref (÷M) | VCO (×N) | Outputs |
|---|---|---|---|
| PLL1 | 24/3 = 8 MHz | 960 MHz | P/2 = **480 MHz SYSCLK**, Q/12 = 80 MHz (SPI1-3, SDMMC1, FDCAN) |
| PLL2 | 24/2 = 12 MHz | 600 MHz | P/3 = 200, Q/6 = 100 MHz (SPI4/5, UARTs), R/3 = 200 MHz |
| PLL3 | 24/6 = 4 MHz | 288 MHz | Q/6 = **48.000 MHz USB (exact)**, R/9 = 32 MHz (ADC, I2C) |

- `ardupilot/hwdef.dat`: `OSCILLATOR_HZ 24000000` plus `MCU_CLOCKRATE_MHZ 480`. The generated `hwdef.h` has `HAL_CUSTOM_MCU_CLOCKRATE 480000000`. ChibiOS sets ODEN, giving VOS0.
- `ardupilot/hwdef-bl.dat`: `OSCILLATOR_HZ 24000000`. The bootloader stays at 400 MHz on the rev Y/X-compatible path.
- **Silicon:** a 960 MHz VCO and 480 MHz are only specified for **revision V** (`REV_ID 0x2003`). ArduPilot does not check the silicon revision at run time. A rev Y part would boot and overclock silently. The requirement is therefore recorded as the `Silicon_Rev` procurement field on U1 and enforced by the verifier.
- The hwdef SPI comment was wrong. ArduPilot's divisor search turns the `16*MHZ` request into **10 MHz on SPI1** (80 MHz kernel clock) and **12.5 MHz on SPI4** (100 MHz kernel clock). The comment now states the real rates.

**2. The KiCad schematic is real now. Before, it was an empty title block.**
`kicad/nano-h743-aio.kicad_sch` (A3, KiCad 8 format 20231120) is generated deterministically by `tools/gen_mcu_core_sch.py`. The generator also writes the project symbol library `kicad/nano-h743-aio.kicad_sym` and `kicad/sym-lib-table`, so the project does not depend on stock libraries being installed.

| Ref | Value | Part (LCSC) | Function |
|---|---|---|---|
| U1 | STM32H743VITx | STM32H743VIT6 (C114409), LQFP-100, **rev V** | MCU, all 100 pins placed |
| Y1 | 24 MHz, CL 12 pF | Yajingxin TXM24M0004322FBCDO00T (C362340), 3225-4P, ESR ≤ 30 Ω, C0 ≤ 5 pF, ±10/±20 ppm | HSE crystal; case pins 2 and 4 to GND |
| C1, C2 | 16 pF | Murata GJM1555C1H160FB01J (C3853959), C0G ±1 % | load caps on OSC_IN and OSC_OUT |
| R1 | 0 Ω | 0402 (C17168) | Rext footprint on OSC_OUT. **Never fit more than 6.8 Ω** |
| FB1 | 600 Ω @ 100 MHz | Murata BLM15AX601SN1D (C76886), Rdc ≤ 0.39 Ω, 500 mA | VDDA ferrite bead |
| R2 | 2.2 Ω | UNI-ROYAL 0402WGF220KTCE (C25101), 1 % | damps the bead-plus-capacitor LC resonance |
| C3/C4, C5/C6 | 1 µF + 100 nF each | CL05A105KA5NQNC (C52923) / CL05B104KO5NNNC (C1525) | at VDDA pin 21 and at VREF+ pin 20 |
| C7, C8 | 2.2 µF | CL10B225KP8NNNC (C100082), X7R | VCAP pins 48 and 73 (LDO, ESR < 100 mΩ) |
| C9–C13, C14, C15 | 5 × 100 nF, 4.7 µF, 100 nF | C1525, C19666 | VDD pins 11/27/50/75/100, bulk, VBAT |
| C16, R3 | 100 nF, 10 kΩ | C1525, C25744 | NRST filter, BOOT0 pull-down |

Net topology: `+3V3 → FB1 → VDDA_FB → R2 → +3.3VA`. The +3.3VA net feeds only VDDA (21), VREF+ (20) and C3–C6. VREF+ is tied to VDDA, which is legal while VREFBUF stays off. VSSA (19) goes to GND. VBAT is tied to VDD because the board has no RTC backup. PC14 and PC15 are left unconnected because there is no LSE.

**3. The MCU pin map is derived from the firmware.** Every GPIO assigned in `hwdef.dat` (43 pins) is broken out with a global label named after its hwdef function, such as `SPI1_SCK`, `IMU1_CS` and `TIM1_CH1`. The other 37 GPIOs get explicit no-connect flags. This closes the Rev 6 open item about `hwdef.dat` being the only record of the pin assignment. Changing a pin in `hwdef.dat` without regenerating the schematic fails gate S1.

### Architecture improvements

- **Functional MCU symbol.** Supplies sit on the top edge, with VBAT plus five VDD on a +3V3 bus and VREF+/VDDA on a separate +3.3VA bus. Returns sit on the bottom edge (five VSS plus VSSA). Clock, reset, boot and VCAP pins are grouped at the top left, and ports A/B (left) and C/D/E (right) are listed in order. Physical pin numbers match KiCad's official `MCU_ST_STM32H7:STM32H743VITx` symbol pin for pin.
- **Crystal design** (`analysis/hse_vdda_analysis.py`; inputs taken from the Y1 datasheet where it gives them):
  - **Load caps:** C = 2 × (CL − Cstray) = 2 × (12 − 4) = **16 pF**, giving CL_eff = 12.00 pF and 0 ppm nominal pull. Over a stray range of 2.5–5.5 pF, ±1 % caps and a motional capacitance up to 8 fF, CL_eff spans 10.42–13.58 pF and the pull spans **+24 / −20 ppm**.
  - **Start-up margin (AN2867):** gm_crit = 4·ESR·(2πf)²·(C0+CL)² = **0.94 mA/V** at the worst corner (ESR 30 Ω, C0 5 pF, CL 13.58 pF). That is a **×1.59 margin** against the STM32H7 HSE limit Gm_critmax = 1.5 mA/V. Required margin is ×1.2.
  - **Substitution rule** (schematic note): a replacement crystal needs ESR_max ≤ 40 Ω at CL 12 pF, or ≤ 20 Ω at CL 20 pF. Typical 18–20 pF / 50 Ω parts fail.
  - **Frequency error over 10 years:** 104 ppm (pull 24 + tolerance 10 + stability 20 + aging 5 ppm/yr). Allowed: 1000 ppm. The tightest consumer is DroneCAN at 1 Mbit/s, which tolerates ≥ 3000 ppm; I applied a 3× margin. USB FS allows 2500 ppm.
  - **Drive level:** DL = ESR·(π·f·Vpp·Ctot)²/2 is 27.6 µW at 1 Vpp and 301 µW at 3.3 Vpp. The datasheet limit is 100 µW, so **Vpp on OSC_OUT must be ≤ 1.90 V**, and this is checked at bring-up. R1 cannot fix an overdrive: anything above 9.8 Ω (6.8 Ω E12) erodes the ×1.2 start-up margin. If bring-up measures more than 1.9 Vpp, change the crystal to a part with a higher drive-level rating.
- **VDDA filter design.** The bead's low-frequency inductance is not specified, so it is swept from 0.47 to 4.7 µH. Bead Rdc is swept from 0.10 to 0.39 Ω. The capacitors are modelled with 45 % DC-bias loss and 1 nH ESL each, and R2 at −1 %.

  | R2 | Worst peaking | DC drop at 10 mA |
  |---|---|---|
  | 0 Ω (bead only) | **+25.0 dB** | 3.9 mV |
  | 1.0 Ω | +5.4 dB (fails) | 14.0 mV |
  | 1.5 Ω | +2.6 dB (only 0.4 dB under the hard limit) | 19.1 mV |
  | **2.2 Ω (selected)** | **+0.5 dB** | **26.1 mV** |

  R2 is chosen by the script: the smallest value with peaking ≤ 2 dB, which leaves a 1 dB guard band under the 3 dB hard limit and keeps the DC drop ≤ 30 mV. Resonance sits between 50 and 211 kHz depending on the corner. Worst-case attenuation is ≥ 29 dB at 1 MHz, ≥ 57 dB at 10 MHz and ≥ 65 dB at 100 MHz. These figures are for SMPS harmonics and MCU core noise. The 26 mV drop is a constant ratiometric offset of 0.8 % on ADC readings, which `BATT_VOLT_MULT` calibration absorbs.
- **Layout rules** (on the schematic sheet, to be applied in the PCB revision): Y1, C1 and C2 within 5 mm of pins 12/13 on the U1 layer, with no vias in the OSC traces. Add a GND guard ring stitched to In1 every 1 mm, with no signals under Y1 on In1. Return C1 and C2 to a GND island tied to VSS pin 10, and keep ESC return currents away from it. Place C3/C4 within 1 mm of pin 21 and C5/C6 within 1 mm of pin 20. Via VSSA straight into a solid, unsplit In1 plane.

### Validation status

| Check | Result |
|---|---|
| `kicad-cli sch erc` (KiCad 8.0.9, all severities) | **0 errors.** 43 warnings, all `global_label_dangling` on hwdef interface labels whose peripherals (IMUs, OSD, ESC, connectors) go on sheets that don't exist yet. |
| `python3 tools/verify_mcu_core_sch.py`: S1 regeneration is byte-identical · S2 ERC · S3 U1 pins match KiCad's official symbol (independent table) · S4 exact node sets for every non-interface net, plus all 43 hwdef pins on the correct LQFP-100 numbers · S5 exact values for all 22 parts, key MPNs, no DNP, rev V field · S7 OSCILLATOR_HZ (fw + bl) equals the Y1 frequency and MCU_CLOCKRATE is 480 | **PASS** (0 failures) |
| Verifier mutation tests: VCAP cap returned to +3V3; VDD decoupling shorted to GND; PA9/PA10 swapped in the generator pin table; NRST cap returned to +3V3; R3 = 1 MΩ; Y1 CL 20 pF; all passives DNP; hwdef pin moved without regenerating; 25 MHz OSCILLATOR_HZ; R2 removed | **every mutation caught**; a no-op control passes |
| `python3 analysis/hse_vdda_analysis.py --ardupilot <tree>` (21 checks; PLL dividers read back from `stm32h7_mcuconf.h`) | **PASS** (0 failures) → `analysis/hse_vdda_report.json` |
| `gcc -E` on ArduPilot `stm32h7_mcuconf.h` | 24 MHz @ 480 resolves M3/N120/P2/Q12, PLL3 M6/N72/Q6. 25 MHz @ 480 hits `#error` (the Rev 6 defect) |
| `python3 tools/validate_dma.py --ardupilot <tree>` (Rev 6 DMA policy, re-run on the new clock) | **PASS** (0 failures, 12/16 streams). Generated `hwdef.h`: `STM32_HSECLK 24000000U`, SYSCLK 480 MHz, SDMMC1/FDCAN 80 MHz, SPI4/5 100 MHz |
| Independent 4-lens adversarial review (crystal math, VDDA/power, KiCad rigour, firmware clock) | All verified findings fixed: C0 3 → 5 pF from the datasheet, aging 3 → 5 ppm/yr, R1 limit 33 → 6.8 Ω, R2 1.0 → 2.2 Ω after widening the bead-L sweep, capacitor ESL added, verifier made exact and non-circular, rev V field, SPI rate comment. Earlier self-checks had already caught 15 pF load caps (+22 ppm corner) and two wrong LCSC codes (C25087 is 200 Ω, not 1 Ω) |
| PCB / Gerbers | Title block and Gerbers regenerated as rev 7.0. **The board has no footprints yet**, so no netlist-to-PCB sync or DRC has been run |
| Full `waf` firmware build / hardware | **Not run.** No ARM toolchain here. Bring-up must do three things: measure Vpp on OSC_OUT with a ≤ 1 pF active probe (gate: ≤ 1.90 V); measure HSE frequency through MCO1 (expect 24 MHz ± 50 ppm at 25 °C); check that `@SYS/uarts.txt` and USB enumeration are good at 480 MHz |

**Open items:** the bead's low-frequency inductance and the crystal's motional capacitance should be confirmed from Murata's SPICE model and the Yajingxin factory data, and the analysis re-run with them. The IMU, OSD, ESC, power and connector sheets are still to be drawn against the labels on this sheet.

## Revision 6.0 Engineering Changelog

**Scope:** ArduPilot `hwdef.dat` DMA stream allocation for USART1, SPI1, SPI4 and the 4-bit microSD on SDMMC1, without DMA conflicts.

### Changes implemented

**`ardupilot/hwdef.dat`: rewritten. The Rev 5 file could not be processed.**
Before this revision, `chibios_hwdef.py` stopped on the first line with `Error: Unable to find module for MCU STM32H743VITx`, so the board definition had never been built. These defects were fixed:

| Defect (Rev 5) | Fix (Rev 6) |
|---|---|
| `MCU STM32H743xx STM32H743VITx` (wrong format) | `MCU STM32H7xx STM32H743xx` |
| Raw `STM32_PLLx_VALUE` lines (not hwdef keywords) | Removed. `stm32h7_mcuconf.h` derives the PLL from `OSCILLATOR_HZ 25000000` |
| Invalid `CONFIG_HAL_BOARD_SUBTYPE`, no `APJ_BOARD_ID` | `APJ_BOARD_ID 5743` (**provisional**, unallocated upstream; must be registered before release) |
| `BIDIR_DSHOT_DMA` (not a real keyword) on all four motors | `BIDIR` on TIM1_CH1 and TIM1_CH3 only. ArduPilot pairs CH1/CH2 and CH3/CH4 for eRPM capture |
| `SPIDEV` lines missing devid and mode, CS given as a pin name | `SPIDEV imuN SPIx DEVID1 IMUn_CS MODE3 2*MHZ 16*MHZ`, `IMU Invensensev3 SPI:imuN` |
| `BARO DPS310:0 …`, `OSD_ENABLED` without `define`, obsolete `CAN_ORDER` | Corrected syntax. OSD font ROMFS added |
| ADC `SCALE(10.9)` on the pin (wrong layer) | Pin `SCALE(1)` plus `HAL_BATT_VOLT/CURR_PIN 10/11` and `HAL_BATT_*_SCALE` |
| No USB, SWD, `SERIAL_ORDER`, storage, LED, beeper, FATFS | Added OTG1 + VBUS, SWD, `SERIAL_ORDER OTG1 USART1 USART2 USART3`, flash storage in sectors 14–15, notify LED, beeper, `HAL_OS_FATFS_IO` |
| TCAN334 STB pin not driven (its internal pull-up holds the transceiver in standby, so the CAN bus is dead) | `PD3 GPIO_CAN1_SILENT OUTPUT LOW` |

**New files**
- `ardupilot/hwdef-bl.dat`: bootloader (USB + USART1 with no DMA, flashing from microSD over SDMMC1, all SPI chip-selects held high).
- `ardupilot/defaults.parm`: bidirectional DShot600 (`SERVO_BLH_BDMASK 15`, 14 poles), RPM-referenced harmonic notch, logging to microSD.
- `tools/validate_dma.py`: runs ArduPilot's own generator and DMA resolver and enforces the DMA policy (see Validation status).

### Architecture: DMA stream map

The STM32H743 has 16 general-purpose streams (DMA1 + DMA2 through DMAMUX1). This is the resolved map from the generated `hwdef.h`:

| Stream | Request | Consumer | Policy |
|---|---|---|---|
| DMA1-0 | TIM1_UP (+ CH1, CH3 capture) | DShot600 out + eRPM in, motors 1–4 | NOSHARE |
| DMA1-1 / 1-2 | SPI1_RX / SPI1_TX | IMU1 ICM-42688-P | NOSHARE |
| DMA1-3 / 1-4 | SPI4_RX / SPI4_TX | IMU2 ICM-42688-P | NOSHARE |
| DMA1-5 / 1-6 | USART1_RX / USART1_TX | MSP DisplayPort / MAVLink2 (≤ 2 Mbaud) | NOSHARE |
| DMA1-7 | ADC1 | Battery voltage and current | dedicated |
| DMA2-0 | USART2_RX | CRSF / ELRS | dedicated |
| DMA2-1 | USART3_RX | GPS | dedicated |
| DMA2-2 / 2-5 | SPI2_TX / SPI2_RX | AT7456E OSD | shareable |
| DMA2-3, 2-4, 2-6, 2-7 | — | **4 spare** | — |

Design decisions:
- **SDMMC1 uses no stream.** On H7 the SDMMC has its own IDMA bus master, which `chibios_hwdef.py` deliberately leaves out of stream allocation. IDMA cannot reach DTCM. ArduPilot's FATFS layer copies through DMA-safe AXI SRAM, so 4-bit logging adds no contention for the IMU or UART streams. Because SDMMC1 occupies PC10/PC11/PC12/PD2, UART4, UART5 and SPI3 can't use those pins.
- **The motor timer uses one stream.** On DMAMUX parts ArduPilot reuses the TIM1_UP stream for TIM1_CHx input capture. This works because bidirectional DShot alternates in time: the frame goes out over UP, then the DMAMUX is switched to CHx to capture the eRPM reply. Different peripherals are not sharing a stream, and `SHARED_DMA_MASK` is `0`.
- **Fewer streams by removing low-value DMA.** I2C1 is excluded from DMA by default on H7. USART2_TX (CRSF telemetry) and USART3_TX (GPS configuration) are `NODMA`, using interrupt-driven transmit for low-volume traffic. That brings usage to 12/16 streams with zero sharing.
- **Policy.** `DMA_NOSHARE TIM1* SPI1* SPI4* USART1*` guarantees the IMUs, motors and the high-rate link are never shared, even if future peripherals use up all streams. `DMA_PRIORITY` sets only the resolver's allocation order. Hardware arbitration priority is fixed by ArduPilot (DShot PL3 > ADC 2 > SPI 1 > USART 0) and can't be changed from the hwdef.

### Validation status

| Check | Result |
|---|---|
| `chibios_hwdef.py` on `hwdef.dat` (firmware) | **PASS**: generates `hwdef.h` (Rev 5: failed at line 1) |
| `chibios_hwdef.py --bootloader` on `hwdef-bl.dat` | **PASS** |
| `python3 tools/validate_dma.py --ardupilot <tree>`: R1 dedicated streams for SPI1, SPI4, USART1 RX/TX and TIM1_UP · R2 no sharing between peripherals · R3 `SHARED_DMA_MASK == 0` · R4 SDMMC1 + FATFS enabled on IDMA · R5 ≤ 16 streams · R6 bootloader generates · R7 single `DMA_PRIORITY`/`DMA_NOSHARE` | **PASS** (0 failures) |
| Negative test: protections removed and UART4/7/8 added | Validator correctly **FAILS** (SPI2 shares streams with UART TX, `SHARED_DMA_MASK != 0`) |
| Independent three-lens review (pins/AF, DMA semantics, params/defines) | 3 defects found and fixed (stray `DMA_PRIORITY` fragment, wrong comment about hardware priority, LED define that nothing read) |
| Full `waf` firmware compile | **Not run.** No `arm-none-eabi` toolchain or compiled `*_bl.bin` in this environment. The validator stages a copy with `AP_BOOTLOADER_FLASHING_ENABLED 0` for that reason only, which does not affect DMA resolution. |
| On hardware | **Pending.** After first flash, read `@SYS/dma.txt` over MAVFTP (expect < 1 % contention on SPI1/SPI4/USART1) and `@SYS/timers.txt` (bidirectional capture active), and run an SD write test at 1 kHz logging. |

**Open items:** register `APJ_BOARD_ID`. The KiCad schematic is still a placeholder title block, so this `hwdef.dat` is currently the only record of the pin assignment and must be carried into the schematic netlist. Confirm the status LED polarity (`OUTPUT LOW`, assumed active-low).

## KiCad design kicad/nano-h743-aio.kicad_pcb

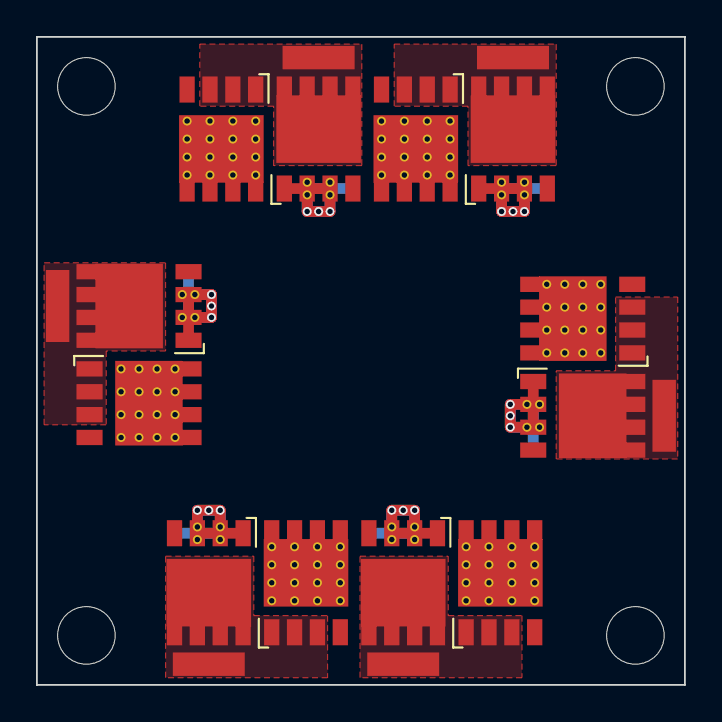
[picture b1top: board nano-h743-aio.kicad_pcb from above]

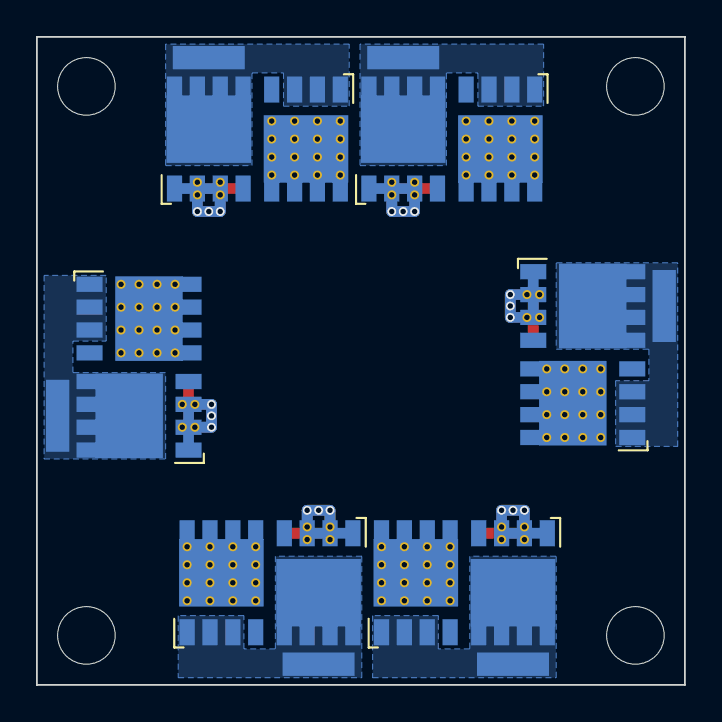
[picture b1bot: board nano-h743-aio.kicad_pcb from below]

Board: 6 copper layers, 36.0 x 36.0 mm, 40 parts (18 on the bottom side), 14 nets.

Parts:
H1, H2, H3, H4: M3_Grommet; MountingHole_3.2mm_M3_Grommet_Keepout
MP1: M1_A; MotorPad_4.0x1.3mm
MP2: M1_B; MotorPad_4.0x1.3mm
MP3: M1_C; MotorPad_4.0x1.3mm
MP4: M2_A; MotorPad_4.0x1.3mm
MP5: M2_B; MotorPad_4.0x1.3mm
MP6: M2_C; MotorPad_4.0x1.3mm
MP7: M3_A; MotorPad_4.0x1.3mm
MP8: M3_B; MotorPad_4.0x1.3mm
MP9: M3_C; MotorPad_4.0x1.3mm
MP10: M4_A; MotorPad_4.0x1.3mm
MP11: M4_B; MotorPad_4.0x1.3mm
MP12: M4_C; MotorPad_4.0x1.3mm
Q1, Q3, Q5, Q7, Q9, Q11: TPHR8504PL; Toshiba_SOP-Advance_TPHR8504PL_ThermalVias_4x4
Q2, Q4, Q6, Q8, Q10, Q12: TPHR8504PL; Toshiba_SOP-Advance_TPHR8504PL_SourceVias_2x2
Q13, Q14, Q15, Q16, Q17, Q18, Q19, Q20, Q21, Q22, Q23, Q24: TPHR8504PL; Toshiba_SOP-Advance_TPHR8504PL

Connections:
ESC1_PH_A: MP1.1, Q1.1, Q1.2, Q1.3, Q2.5, Q2.6, Q2.7, Q2.8
ESC1_PH_B: MP2.1, Q3.1, Q3.2, Q3.3, Q4.5, Q4.6, Q4.7, Q4.8
ESC1_PH_C: MP3.1, Q5.1, Q5.2, Q5.3, Q6.5, Q6.6, Q6.7, Q6.8
ESC2_PH_A: MP4.1, Q7.1, Q7.2, Q7.3, Q8.5, Q8.6, Q8.7, Q8.8
ESC2_PH_B: MP5.1, Q9.1, Q9.2, Q9.3, Q10.5, Q10.6, Q10.7, Q10.8
ESC2_PH_C: MP6.1, Q11.1, Q11.2, Q11.3, Q12.5, Q12.6, Q12.7, Q12.8
ESC3_PH_A: MP7.1, Q13.1, Q13.2, Q13.3, Q14.5, Q14.6, Q14.7, Q14.8
ESC3_PH_B: MP8.1, Q15.1, Q15.2, Q15.3, Q16.5, Q16.6, Q16.7, Q16.8
ESC3_PH_C: MP9.1, Q17.1, Q17.2, Q17.3, Q18.5, Q18.6, Q18.7, Q18.8
ESC4_PH_A: MP10.1, Q19.1, Q19.2, Q19.3, Q20.5, Q20.6, Q20.7, Q20.8
ESC4_PH_B: MP11.1, Q21.1, Q21.2, Q21.3, Q22.5, Q22.6, Q22.7, Q22.8
ESC4_PH_C: MP12.1, Q23.1, Q23.2, Q23.3, Q24.5, Q24.6, Q24.7, Q24.8
GND: Q2.1, Q2.2, Q2.3, Q4.1, Q4.2, Q4.3, Q6.1, Q6.2, Q6.3, Q8.1, Q8.2, Q8.3, Q10.1, Q10.2, Q10.3, Q12.1, Q12.2, Q12.3, Q14.1, Q14.2, Q14.3, Q16.1, Q16.2, Q16.3, Q18.1, Q18.2, Q18.3, Q20.1, Q20.2, Q20.3, Q22.1, Q22.2, Q22.3, Q24.1, Q24.2, Q24.3
VBAT: Q1.5, Q1.6, Q1.7, Q1.8, Q3.5, Q3.6, Q3.7, Q3.8, Q5.5, Q5.6, Q5.7, Q5.8, Q7.5, Q7.6, Q7.7, Q7.8, Q9.5, Q9.6, Q9.7, Q9.8, Q11.5, Q11.6, Q11.7, Q11.8, Q13.5, Q13.6, Q13.7, Q13.8, Q15.5, Q15.6, Q15.7, Q15.8, Q17.5, Q17.6, Q17.7, Q17.8, Q19.5, Q19.6, Q19.7, Q19.8, Q21.5, Q21.6, Q21.7, Q21.8, Q23.5, Q23.6, Q23.7, Q23.8
